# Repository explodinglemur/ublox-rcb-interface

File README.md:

# ublox-rcb-interface
USB/RS232 interface board for F9P/M8T and other ublox RCB eval boards

Provides TX out and PPS from receiver to both USB and RS232 interfaces, and jumper-selectable TX from either USB or RS232 to receiver.

USB interface may also be disabled so it does not enumerate and only provides power.

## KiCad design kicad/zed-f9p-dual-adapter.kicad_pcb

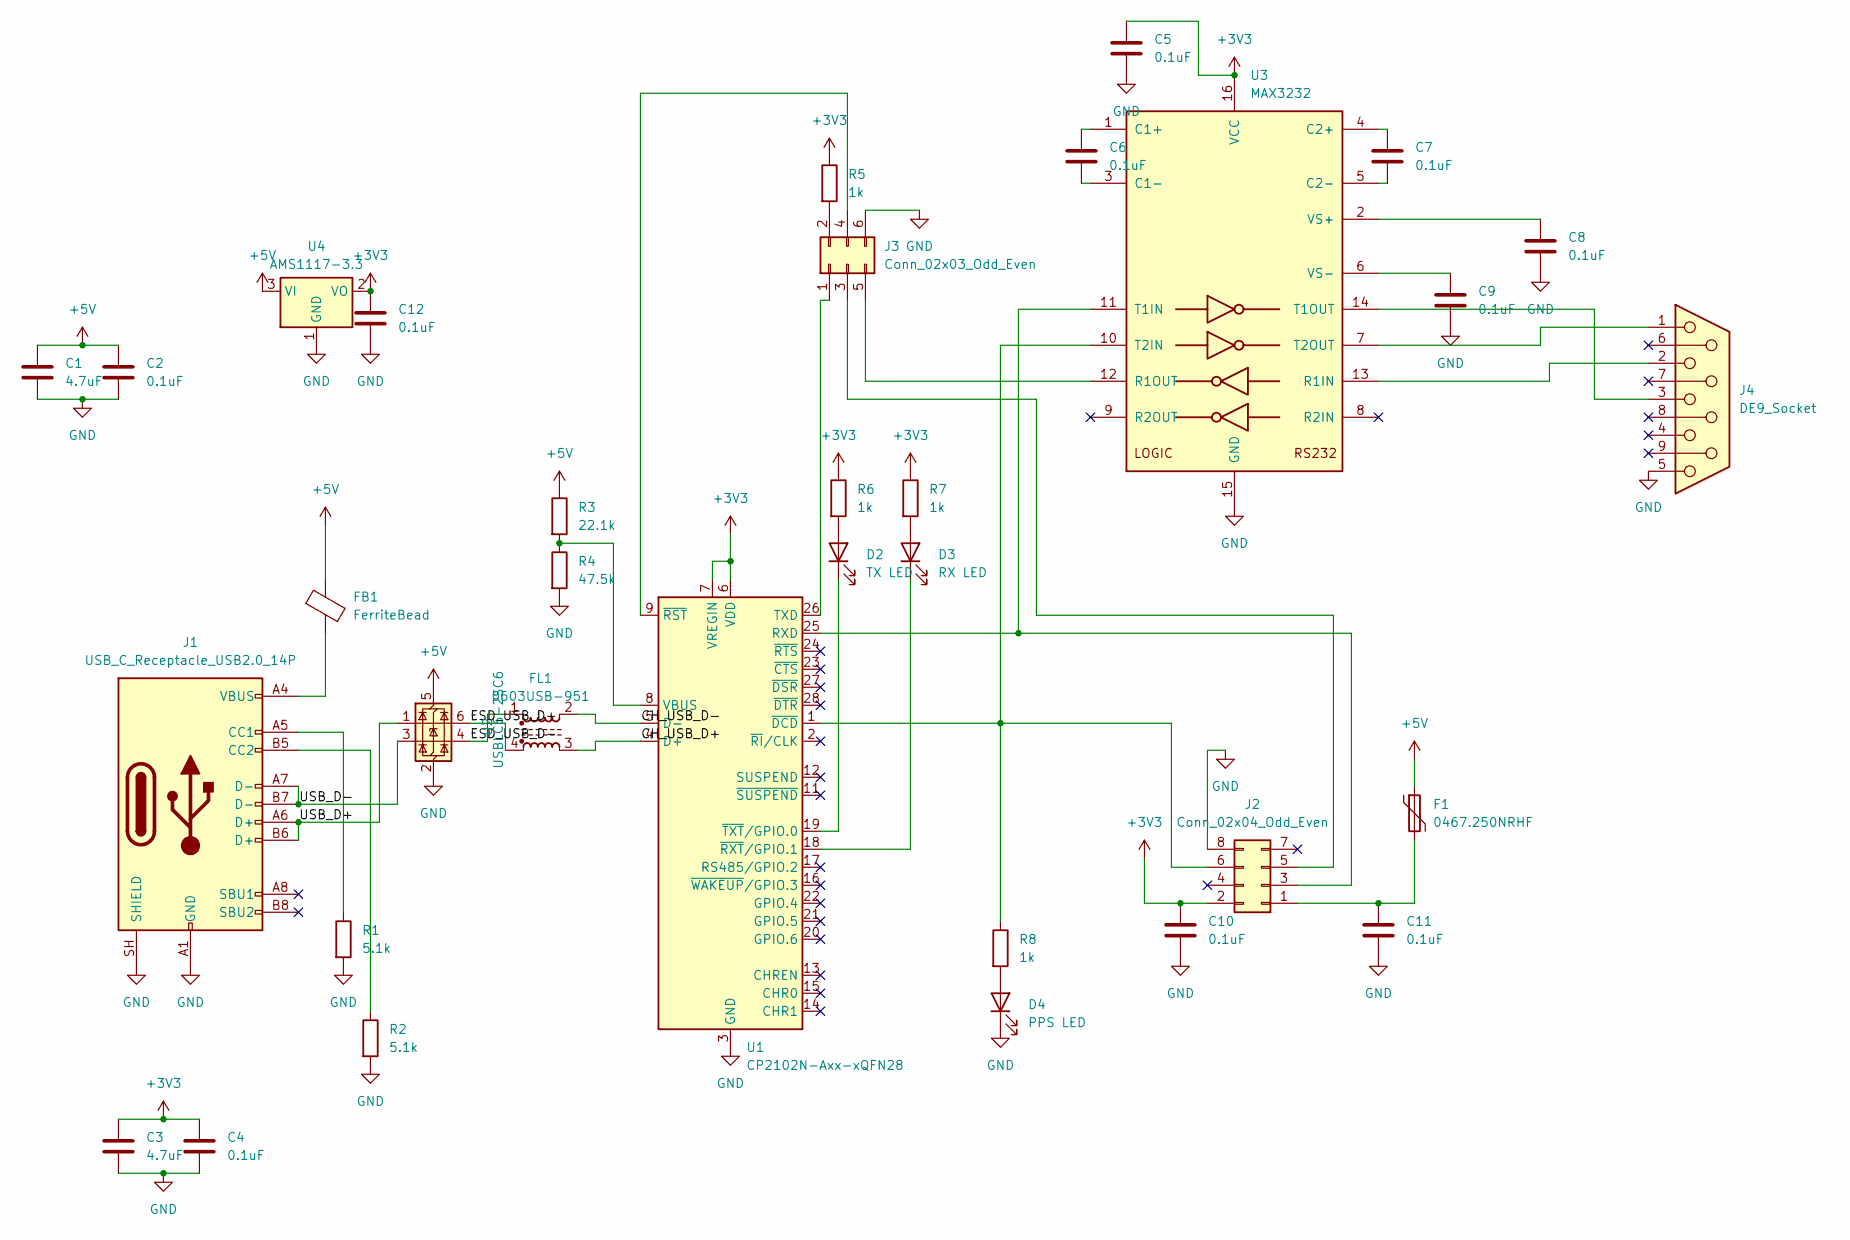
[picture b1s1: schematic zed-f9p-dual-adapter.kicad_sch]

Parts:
C1, C3: 4.7uF; C_0402_1005Metric
C2, C4, C5, C6, C7, C8, C9, C10, C11, C12: 0.1uF; C_0402_1005Metric
D2: TX LED; LED_0402_1005Metric
D3: RX LED; LED_0402_1005Metric
D4: PPS LED; LED_0402_1005Metric
F1: 0467.250NRHF; Fuse_0603_1608Metric
FB1: FerriteBead; L_0805_2012Metric
FL1: 0603USB-951; L_CommonModeChoke_Coilcraft_0603USB
J1: USB_C_Receptacle_USB2.0_14P; USB_C_Receptacle_G-Switch_GT-USB-7010ASV
J2: Conn_02x04_Odd_Even; PinSocket_2x04_P2.00mm_Vertical_SMD
J3: Conn_02x03_Odd_Even; PinHeader_2x03_P2.54mm_Vertical_SMD
J4: DE9_Socket; DSUB-9_Socket_EdgeMount_P2.77mm
R1, R2: 5.1k; R_0402_1005Metric
R3: 22.1k; R_0402_1005Metric
R4: 47.5k; R_0402_1005Metric
R5, R6, R7, R8: 1k; R_0402_1005Metric
U1: CP2102N-Axx-xQFN28; QFN-28-1EP_5x5mm_P0.5mm_EP3.35x3.35mm
U2: USBLC6-2SC6; SOT-666
U3: MAX3232; SSOP-16_5.3x6.2mm_P0.65mm
U4: AMS1117-3.3; SOT-223-3_TabPin2

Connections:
+3V3: C3.1, C4.1, C5.1, C10.1, C12.1, J2.2, R5.1, R6.1, R7.1, U1.6 (VDD), U1.7 (VREGIN), U3.16 (VCC), U4.2 (VO)
+5V: C1.1, C2.1, F1.1, FB1.1, R3.1, U2.5 (VBUS), U4.3 (VI)
/CH_USB_D+: FL1.3, U1.4 (D+)
/CH_USB_D-: FL1.2, U1.5 (D-)
/ESD_USB_D+: FL1.4, U2.6 (I/O1)
/ESD_USB_D-: FL1.1, U2.4 (I/O2)
/USB_D+: J1.A6 (D+), J1.B6 (D+), U2.1 (I/O1)
/USB_D-: J1.A7 (D-), J1.B7 (D-), U2.3 (I/O2)
GND: C1.2, C2.2, C3.2, C4.2, C5.2, C8.2, C9.2, C10.2, C11.2, C12.2, D4.1 (K), J1.A1 (GND), J1.A12 (GND), J1.B1 (GND), J1.B12 (GND), J1.SH (SHIELD), J2.8, J3.6, J4.5, R1.2, R2.2, R4.2, U1.3 (GND), U1.29 (GND), U2.2 (GND), U3.15 (GND), U4.1 (GND)
unnamed: D2.2 (A), R6.2
unnamed: D2.1 (K), U1.19 (~TXT/GPIO.0)
unnamed: D3.2 (A), R7.2
unnamed: D3.1 (K), U1.18 (~RXT/GPIO.1)
unnamed: D4.2 (A), R8.2
unnamed: FB1.2, J1.A4 (VBUS), J1.A9 (VBUS), J1.B4 (VBUS), J1.B9 (VBUS)
unnamed: J1.A5 (CC1), R1.1
unnamed: J1.B5 (CC2), R2.1
unnamed: C11.1, F1.2, J2.1
unnamed: J2.3, U1.25 (RXD), U3.11 (T1IN)
unnamed: J2.5, J3.3
unnamed: J2.6, R8.1, U1.1 (~DCD), U3.10 (T2IN)
unnamed: J3.1, U1.26 (TXD)
unnamed: J3.2, R5.2
unnamed: J3.4, U1.9 (~RST)
unnamed: J3.5, U3.12 (R1OUT)
unnamed: R3.2, R4.1, U1.8 (VBUS)
unnamed: C6.1, U3.1 (C1+)
unnamed: C6.2, U3.3 (C1-)
unnamed: C7.1, U3.4 (C2+)
unnamed: C7.2, U3.5 (C2-)
unnamed: J4.2, U3.13 (R1IN)
unnamed: J4.3, U3.14 (T1OUT)
unnamed: J4.1, U3.7 (T2OUT)
unnamed: C8.1, U3.2 (VS+)
unnamed: C9.1, U3.6 (VS-)

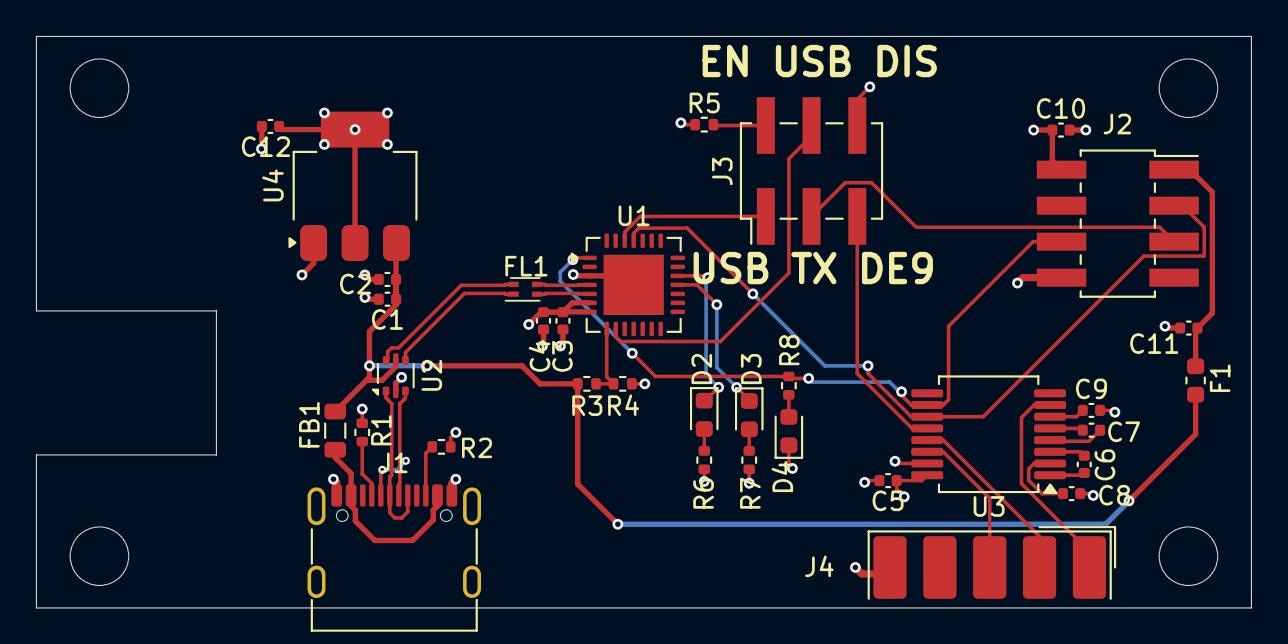
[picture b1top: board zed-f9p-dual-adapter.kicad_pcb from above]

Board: 4 copper layers, 67.5 x 31.8 mm, 34 parts (0 on the bottom side), 35 nets.

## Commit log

2026-05-13 Create LICENSE
    CERN OHL v2 weakly reciprocal license
2026-05-15 Add files via upload
    Updated layout to improve manufacturability

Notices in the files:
kicad/zed-f9p-dual-adapter.kicad_pcb:
CERN-OHL-W v2.0
